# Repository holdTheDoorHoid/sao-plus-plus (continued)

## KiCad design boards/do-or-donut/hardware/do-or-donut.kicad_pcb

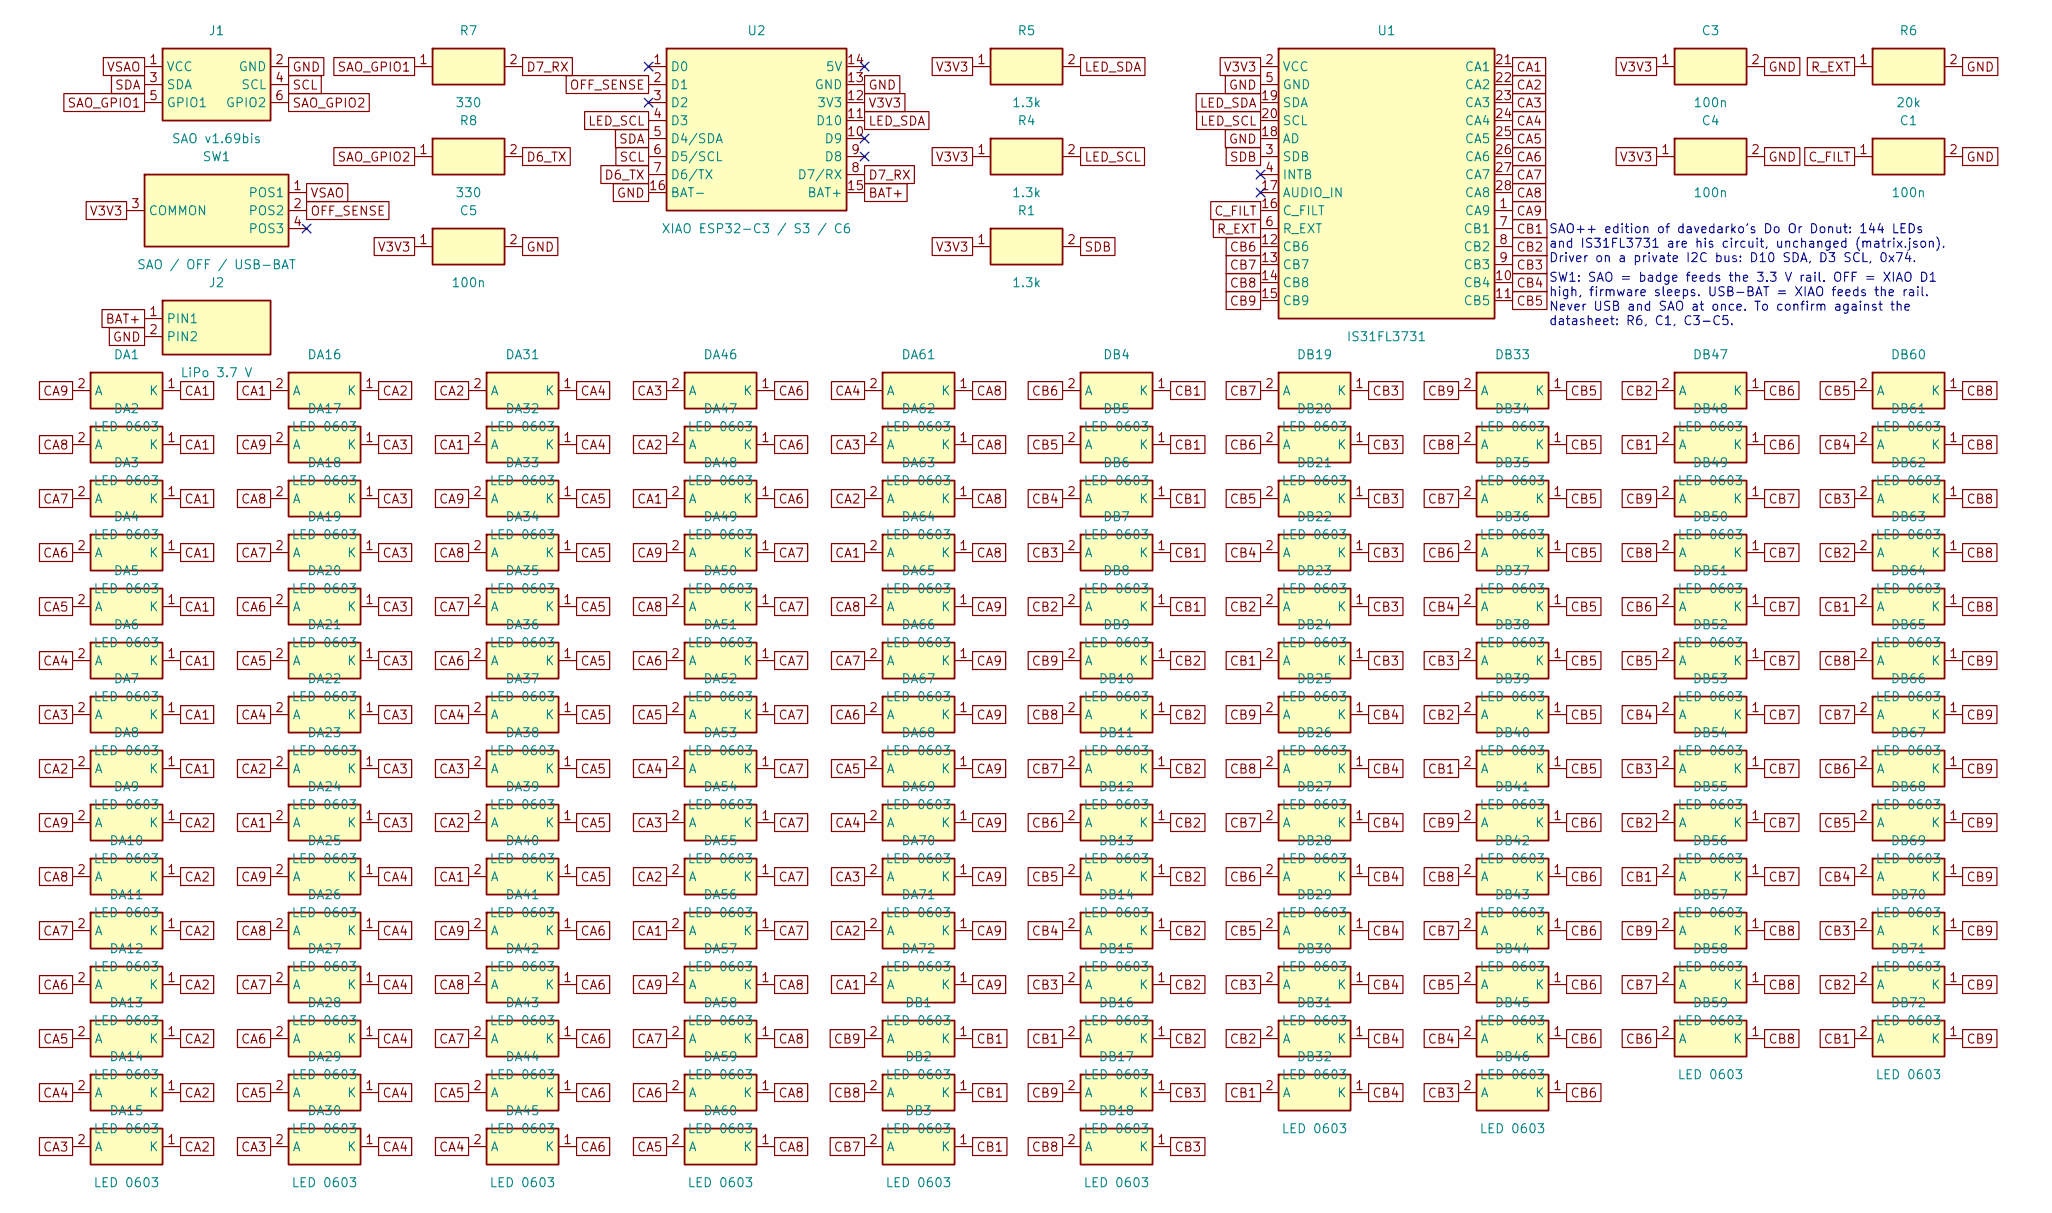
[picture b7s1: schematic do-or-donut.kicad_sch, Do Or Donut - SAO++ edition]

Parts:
C1, C3, C4, C5: 100n; SAOPP_C_0603_1608Metric; MPN CC0603KRX7R9BB104; LCSC C14663
DA1, DA2, DA3, DA4, DA5, DA6, DA7, DA8, DA9, DA10, DA11, DA12, DA13, DA14, DA15, DA16, DA17, DA18, DA19, DA20, DA21, DA22, DA23, DA24, DA25, DA26, DA27, DA28, DA29, DA30, DA31, DA32, DA33, DA34, DA35, DA36, DA37, DA38, DA39, DA40, DA41, DA42, DA43, DA44, DA45, DA46, DA47, DA48, DA49, DA50, DA51, DA52, DA53, DA54, DA55, DA56, DA57, DA58, DA59, DA60, DA61, DA62, DA63, DA64, DA65, DA66, DA67, DA68, DA69, DA70, DA71, DA72: LED 0603; LED_0603_CHIP-LED0603_davedarko; MPN 0603 LED, colour to be chosen
DB1, DB2, DB3, DB4, DB5, DB6, DB7, DB8, DB9, DB10, DB11, DB12, DB13, DB14, DB15, DB16, DB17, DB18, DB19, DB20, DB21, DB22, DB23, DB24, DB25, DB26, DB27, DB28, DB29, DB30, DB31, DB32, DB33, DB34, DB35, DB36, DB37, DB38, DB39, DB40, DB41, DB42, DB43, DB44, DB45, DB46, DB47, DB48, DB49, DB50, DB51, DB52, DB53, DB54, DB55, DB56, DB57, DB58, DB59, DB60, DB61, DB62, DB63, DB64, DB65, DB66, DB67, DB68, DB69, DB70, DB71, DB72: LED 0603; LED_0603_CHIP-LED0603_davedarko; MPN 0603 LED, colour to be chosen
J1: SAO v1.69bis; SAOPP_CONN-01_BoxHeader_2x03_P2.54mm_SMD_XFCN_BH254VS-6P; MPN BH254VS-6P; LCSC C492445
J2: LiPo 3.7 V; SAOPP_CONN-10_JST_PH_S2B-PH-SM4-TB_1x02_Horizontal; MPN S2B-PH-SM4-TB(LF)(SN); LCSC C295747
R1, R4, R5: 1.3k; SAOPP_R_0603_1608Metric; MPN 0603WAF1301T5E; LCSC C22767
R6: 20k; R_0603_1608Metric; MPN 0603WAF2002T5E; LCSC C4184
R7, R8: 330; SAOPP_R_0603_1608Metric; MPN 0603WAF3300T5E; LCSC C23138
SW1: SAO / OFF / USB-BAT; SAOPP_SW-01_Slide_SP3T_CK_PCM13SMTR; MPN PCM13SMTR; LCSC C221842
U1: IS31FL3731; SSOP-28_IS31FL3731_davedarko; MPN IS31FL3731-SALS2-TR; LCSC C2940545
U2: XIAO ESP32-C3 / S3 / C6; SAOPP_MCU-01_Seeed_XIAO_SMD_C3_S3_C6; MPN XIAO ESP32-C3 / S3 / C6

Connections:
BAT+: J2.1 (PIN1), U2.15 (BAT+)
CA1: DA1.1 (K), DA2.1 (K), DA3.1 (K), DA4.1 (K), DA5.1 (K), DA6.1 (K), DA7.1 (K), DA8.1 (K), DA16.2 (A), DA24.2 (A), DA32.2 (A), DA40.2 (A), DA48.2 (A), DA56.2 (A), DA64.2 (A), DA72.2 (A), U1.21 (CA1)
CA2: DA8.2 (A), DA9.1 (K), DA10.1 (K), DA11.1 (K), DA12.1 (K), DA13.1 (K), DA14.1 (K), DA15.1 (K), DA16.1 (K), DA23.2 (A), DA31.2 (A), DA39.2 (A), DA47.2 (A), DA55.2 (A), DA63.2 (A), DA71.2 (A), U1.22 (CA2)
CA3: DA7.2 (A), DA15.2 (A), DA17.1 (K), DA18.1 (K), DA19.1 (K), DA20.1 (K), DA21.1 (K), DA22.1 (K), DA23.1 (K), DA24.1 (K), DA30.2 (A), DA38.2 (A), DA46.2 (A), DA54.2 (A), DA62.2 (A), DA70.2 (A), U1.23 (CA3)
CA4: DA6.2 (A), DA14.2 (A), DA22.2 (A), DA25.1 (K), DA26.1 (K), DA27.1 (K), DA28.1 (K), DA29.1 (K), DA30.1 (K), DA31.1 (K), DA32.1 (K), DA37.2 (A), DA45.2 (A), DA53.2 (A), DA61.2 (A), DA69.2 (A), U1.24 (CA4)
CA5: DA5.2 (A), DA13.2 (A), DA21.2 (A), DA29.2 (A), DA33.1 (K), DA34.1 (K), DA35.1 (K), DA36.1 (K), DA37.1 (K), DA38.1 (K), DA39.1 (K), DA40.1 (K), DA44.2 (A), DA52.2 (A), DA60.2 (A), DA68.2 (A), U1.25 (CA5)
CA6: DA4.2 (A), DA12.2 (A), DA20.2 (A), DA28.2 (A), DA36.2 (A), DA41.1 (K), DA42.1 (K), DA43.1 (K), DA44.1 (K), DA45.1 (K), DA46.1 (K), DA47.1 (K), DA48.1 (K), DA51.2 (A), DA59.2 (A), DA67.2 (A), U1.26 (CA6)
CA7: DA3.2 (A), DA11.2 (A), DA19.2 (A), DA27.2 (A), DA35.2 (A), DA43.2 (A), DA49.1 (K), DA50.1 (K), DA51.1 (K), DA52.1 (K), DA53.1 (K), DA54.1 (K), DA55.1 (K), DA56.1 (K), DA58.2 (A), DA66.2 (A), U1.27 (CA7)
CA8: DA2.2 (A), DA10.2 (A), DA18.2 (A), DA26.2 (A), DA34.2 (A), DA42.2 (A), DA50.2 (A), DA57.1 (K), DA58.1 (K), DA59.1 (K), DA60.1 (K), DA61.1 (K), DA62.1 (K), DA63.1 (K), DA64.1 (K), DA65.2 (A), U1.28 (CA8)
CA9: DA1.2 (A), DA9.2 (A), DA17.2 (A), DA25.2 (A), DA33.2 (A), DA41.2 (A), DA49.2 (A), DA57.2 (A), DA65.1 (K), DA66.1 (K), DA67.1 (K), DA68.1 (K), DA69.1 (K), DA70.1 (K), DA71.1 (K), DA72.1 (K), U1.1 (CA9)
CB1: DB1.1 (K), DB2.1 (K), DB3.1 (K), DB4.1 (K), DB5.1 (K), DB6.1 (K), DB7.1 (K), DB8.1 (K), DB16.2 (A), DB24.2 (A), DB32.2 (A), DB40.2 (A), DB48.2 (A), DB56.2 (A), DB64.2 (A), DB72.2 (A), U1.7 (CB1)
CB2: DB8.2 (A), DB9.1 (K), DB10.1 (K), DB11.1 (K), DB12.1 (K), DB13.1 (K), DB14.1 (K), DB15.1 (K), DB16.1 (K), DB23.2 (A), DB31.2 (A), DB39.2 (A), DB47.2 (A), DB55.2 (A), DB63.2 (A), DB71.2 (A), U1.8 (CB2)
CB3: DB7.2 (A), DB15.2 (A), DB17.1 (K), DB18.1 (K), DB19.1 (K), DB20.1 (K), DB21.1 (K), DB22.1 (K), DB23.1 (K), DB24.1 (K), DB30.2 (A), DB38.2 (A), DB46.2 (A), DB54.2 (A), DB62.2 (A), DB70.2 (A), U1.9 (CB3)
CB4: DB6.2 (A), DB14.2 (A), DB22.2 (A), DB25.1 (K), DB26.1 (K), DB27.1 (K), DB28.1 (K), DB29.1 (K), DB30.1 (K), DB31.1 (K), DB32.1 (K), DB37.2 (A), DB45.2 (A), DB53.2 (A), DB61.2 (A), DB69.2 (A), U1.10 (CB4)
CB5: DB5.2 (A), DB13.2 (A), DB21.2 (A), DB29.2 (A), DB33.1 (K), DB34.1 (K), DB35.1 (K), DB36.1 (K), DB37.1 (K), DB38.1 (K), DB39.1 (K), DB40.1 (K), DB44.2 (A), DB52.2 (A), DB60.2 (A), DB68.2 (A), U1.11 (CB5)
CB6: DB4.2 (A), DB12.2 (A), DB20.2 (A), DB28.2 (A), DB36.2 (A), DB41.1 (K), DB42.1 (K), DB43.1 (K), DB44.1 (K), DB45.1 (K), DB46.1 (K), DB47.1 (K), DB48.1 (K), DB51.2 (A), DB59.2 (A), DB67.2 (A), U1.12 (CB6)
CB7: DB3.2 (A), DB11.2 (A), DB19.2 (A), DB27.2 (A), DB35.2 (A), DB43.2 (A), DB49.1 (K), DB50.1 (K), DB51.1 (K), DB52.1 (K), DB53.1 (K), DB54.1 (K), DB55.1 (K), DB56.1 (K), DB58.2 (A), DB66.2 (A), U1.13 (CB7)
CB8: DB2.2 (A), DB10.2 (A), DB18.2 (A), DB26.2 (A), DB34.2 (A), DB42.2 (A), DB50.2 (A), DB57.1 (K), DB58.1 (K), DB59.1 (K), DB60.1 (K), DB61.1 (K), DB62.1 (K), DB63.1 (K), DB64.1 (K), DB65.2 (A), U1.14 (CB8)
CB9: DB1.2 (A), DB9.2 (A), DB17.2 (A), DB25.2 (A), DB33.2 (A), DB41.2 (A), DB49.2 (A), DB57.2 (A), DB65.1 (K), DB66.1 (K), DB67.1 (K), DB68.1 (K), DB69.1 (K), DB70.1 (K), DB71.1 (K), DB72.1 (K), U1.15 (CB9)
C_FILT: C1.1, U1.16 (C_FILT)
D6_TX: R8.2, U2.7 (D6/TX)
D7_RX: R7.2, U2.8 (D7/RX)
GND: C1.2, C3.2, C4.2, C5.2, J1.2 (GND), J2.2 (PIN2), R6.2, U1.5 (GND), U1.18 (AD), U2.13 (GND), U2.16 (BAT-)
LED_SCL: R4.2, U1.20 (SCL), U2.4 (D3)
LED_SDA: R5.2, U1.19 (SDA), U2.11 (D10)
OFF_SENSE: SW1.2 (POS2), U2.2 (D1)
R_EXT: R6.1, U1.6 (R_EXT)
SAO_GPIO1: J1.5 (GPIO1), R7.1
SAO_GPIO2: J1.6 (GPIO2), R8.1
SCL: J1.4 (SCL), U2.6 (D5/SCL)
SDA: J1.3 (SDA), U2.5 (D4/SDA)
SDB: R1.2, U1.3 (SDB)
V3V3: C3.1, C4.1, C5.1, R1.1, R4.1, R5.1, SW1.3 (COMMON), U1.2 (VCC), U2.12 (3V3)
VSAO: J1.1 (VCC), SW1.1 (POS1)

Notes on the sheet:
SAO++ edition of davedarko's Do Or Donut: 144 LEDs and IS31FL3731 are his circuit, unchanged (matrix.json). Driver on a private I2C bus: D10 SDA, D3 SCL, 0x74.
SW1: SAO = badge feeds the 3.3 V rail. OFF = XIAO D1 high, firmware sleeps. USB-BAT = XIAO feeds the rail. Never USB and SAO at once. To confirm against the datasheet: R6, C1, C3-C5.

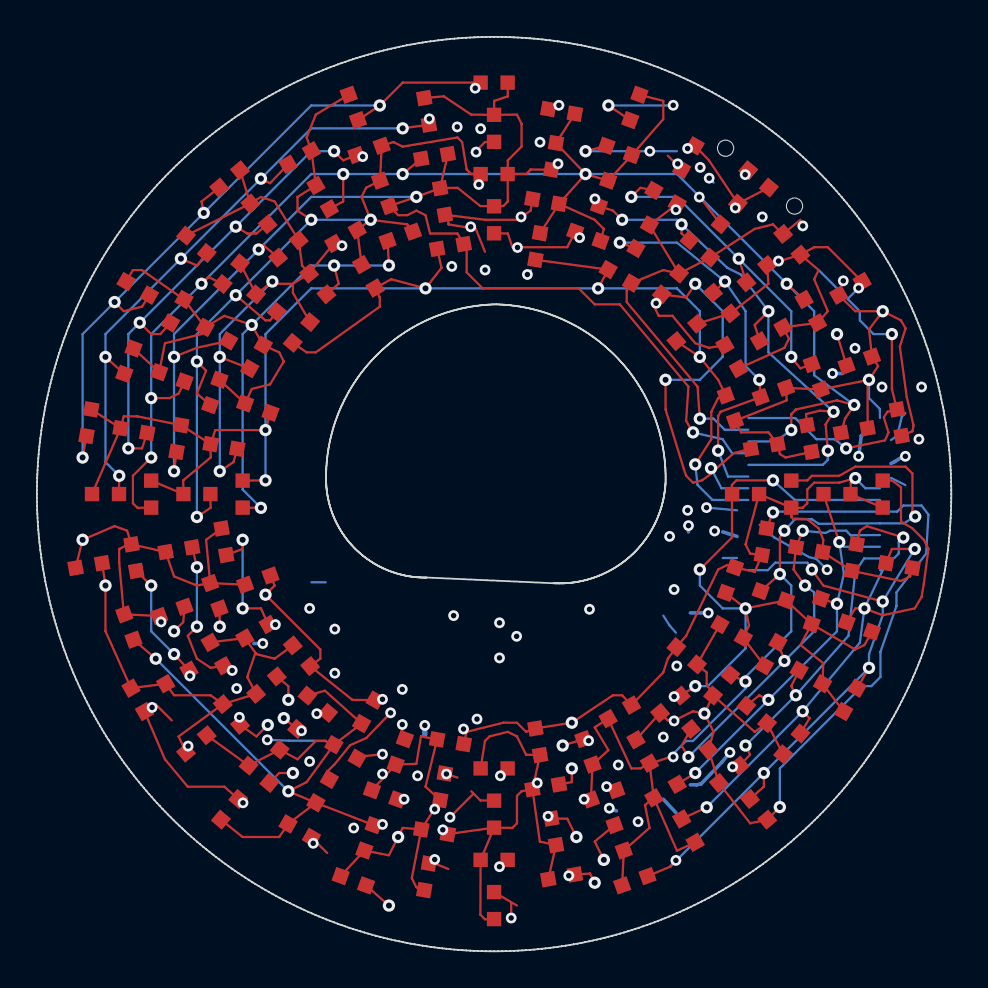
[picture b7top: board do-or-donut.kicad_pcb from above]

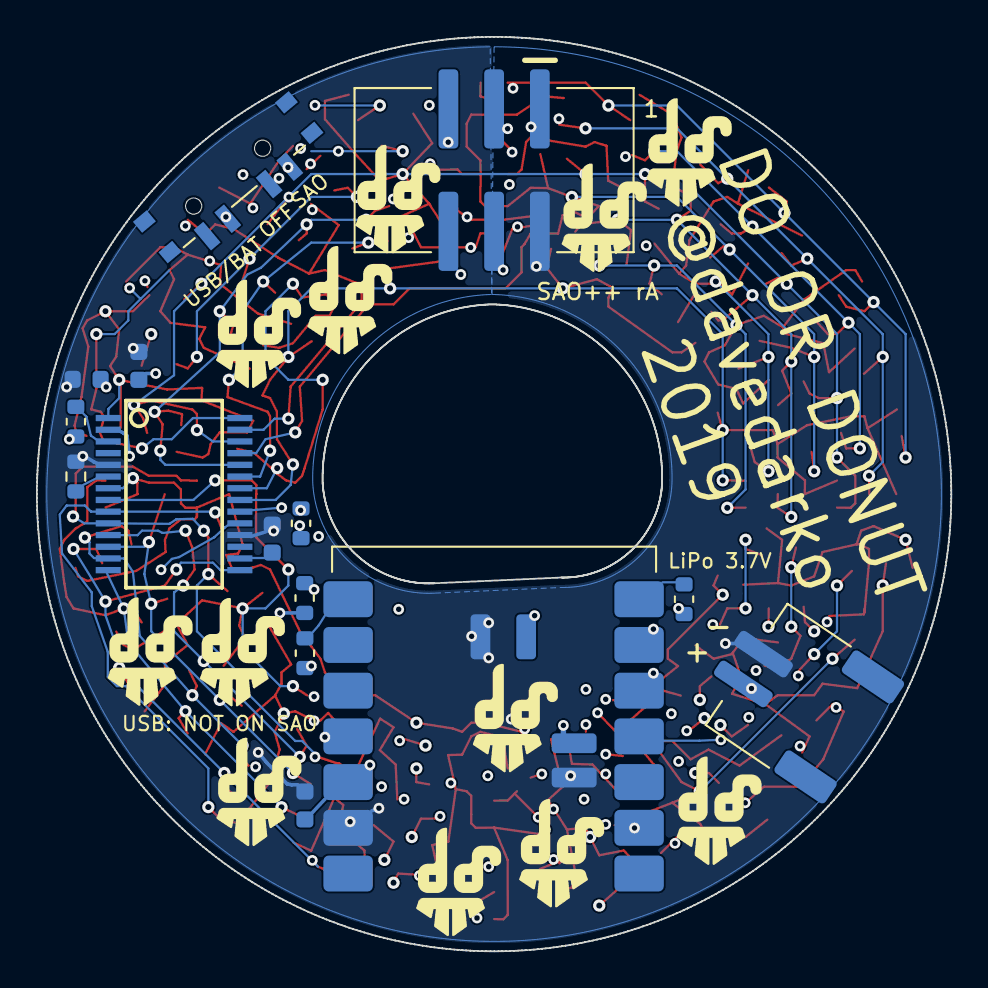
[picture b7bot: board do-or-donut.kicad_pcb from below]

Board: 4 copper layers, 50.8 x 50.8 mm, 159 parts (15 on the bottom side), 34 nets.

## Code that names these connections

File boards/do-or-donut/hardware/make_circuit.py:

#!/usr/bin/env python3
"""Write hardware/circuit.json (the circuit as data) for Do Or Donut.

  python3 boards/do-or-donut/hardware/make_circuit.py

The 144 LEDs come from matrix.json (the maker's wiring, extracted and checked by extract_matrix.py); everything else
is listed here. tools/gen_schematic.py and build_board.py both read circuit.json. Schematic positions are on a 2.54 grid.
"""
import json
from pathlib import Path

HERE = Path(__file__).resolve().parent
M = json.loads((HERE / "matrix.json").read_text())

parts = [
    {"ref": "J1", "symbol": "SAO_Connector_v1.69bis", "at": [33.02, 17.78],
     "nets": {"1": "VSAO", "2": "GND", "3": "SDA", "4": "SCL", "5": "SAO_GPIO1", "6": "SAO_GPIO2"}},
    {"ref": "SW1", "symbol": "Power_Switch_SP3T_PCM13", "at": [33.02, 35.56], "value": "SAO / OFF / USB-BAT",
     "nets": {"3": "V3V3", "1": "VSAO", "2": "OFF_SENSE"}},
    {"ref": "J2", "symbol": "LiPo_Connector_JST_PH", "at": [33.02, 53.34], "nets": {"1": "BAT+", "2": "GND"}},
    {"ref": "R7", "symbol": "R_Series_330", "at": [68.58, 17.78], "nets": {"1": "SAO_GPIO1", "2": "D7_RX"}},
    {"ref": "R8", "symbol": "R_Series_330", "at": [68.58, 30.48], "nets": {"1": "SAO_GPIO2", "2": "D6_TX"}},
    {"ref": "C5", "symbol": "C_100n", "at": [68.58, 43.18], "nets": {"1": "V3V3", "2": "GND"}},
    {"ref": "U2", "symbol": "XIAO_ESP32_Module", "at": [109.22, 17.78],
     "nets": {"2": "OFF_SENSE", "4": "LED_SCL", "5": "SDA", "6": "SCL", "7": "D6_TX", "8": "D7_RX",
              "11": "LED_SDA", "12": "V3V3", "13": "GND", "15": "BAT+", "16": "GND"}},
    {"ref": "R5", "symbol": "R_LED_1k3", "at": [147.32, 17.78], "value": "1.3k", "nets": {"1": "V3V3", "2": "LED_SDA"}},
    {"ref": "R4", "symbol": "R_LED_1k3", "at": [147.32, 30.48], "value": "1.3k", "nets": {"1": "V3V3", "2": "LED_SCL"}},
    {"ref": "R1", "symbol": "R_LED_1k3", "at": [147.32, 43.18], "value": "1.3k", "nets": {"1": "V3V3", "2": "SDB"}},
    {"ref": "R6", "symbol": "R_20k", "at": [271.78, 17.78], "nets": {"1": "R_EXT", "2": "GND"}},
    {"ref": "C1", "symbol": "C_100n", "at": [271.78, 30.48], "nets": {"1": "C_FILT", "2": "GND"}},
    {"ref": "U1", "symbol": "IS31FL3731_SSOP28", "at": [198.12, 17.78],
     "nets": {"2": "V3V3", "5": "GND", "19": "LED_SDA", "20": "LED_SCL", "18": "GND", "3": "SDB", "16": "C_FILT", "6": "R_EXT"}
     | {str(p): n for n, p in M["driver"]["pins"].items()}},
    {"ref": "C3", "symbol": "C_100n", "at": [243.84, 17.78], "nets": {"1": "V3V3", "2": "GND"}},
    {"ref": "C4", "symbol": "C_100n", "at": [243.84, 30.48], "nets": {"1": "V3V3", "2": "GND"}},
]
# LEDs in reference order, 10 columns (shorter ones on the right, clear of the title block)
HEIGHTS = [15, 15, 15, 15, 15, 15, 14, 14, 13, 13]
slots = [(c, r) for c, hgt in enumerate(HEIGHTS) for r in range(hgt)]
for k, d in enumerate(M["leds"]):
    c, r = slots[k]
    parts.append({"ref": d["ref"], "symbol": "LED_0603_Matrix", "at": [20.32 + c * 27.94, round(63.5 + r * 7.62, 2)],
                  "nets": {"2": d["anode"], "1": d["cathode"]}})

notes = [
    ["SAO++ edition of davedarko's Do Or Donut: 144 LEDs\\nand IS31FL3731 are his circuit, unchanged (matrix.json).\\nDriver on a private I2C bus: D10 SDA, D3 SCL, 0x74.", [220.98, 45.72]],
    ["SW1: SAO = badge feeds the 3.3 V rail. OFF = XIAO D1\\nhigh, firmware sleeps. USB-BAT = XIAO feeds the rail.\\nNever USB and SAO at once. To confirm against the\\ndatasheet: R6, C1, C3-C5.", [220.98, 54.61]],
]
c = {"title": "Do Or Donut - SAO++ edition", "rev": "A",
     "credit": "Original design: davedarko (Dave Darko), 2019, github.com/davedarko/Simple-Add-ons-SAO",
     "parts": parts, "notes": notes}
(HERE / "circuit.json").write_text(json.dumps(c, indent=1) + "\n")
print("circuit.json:", len(parts), "parts")
